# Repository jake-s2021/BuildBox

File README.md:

# BuildBox
Respository containing the files to make a BuildBox leverless arcade stick

The G-Code Files are for an Elegoo Neptune 3 Pro, if you have another printer, do not use them; Slice your own.

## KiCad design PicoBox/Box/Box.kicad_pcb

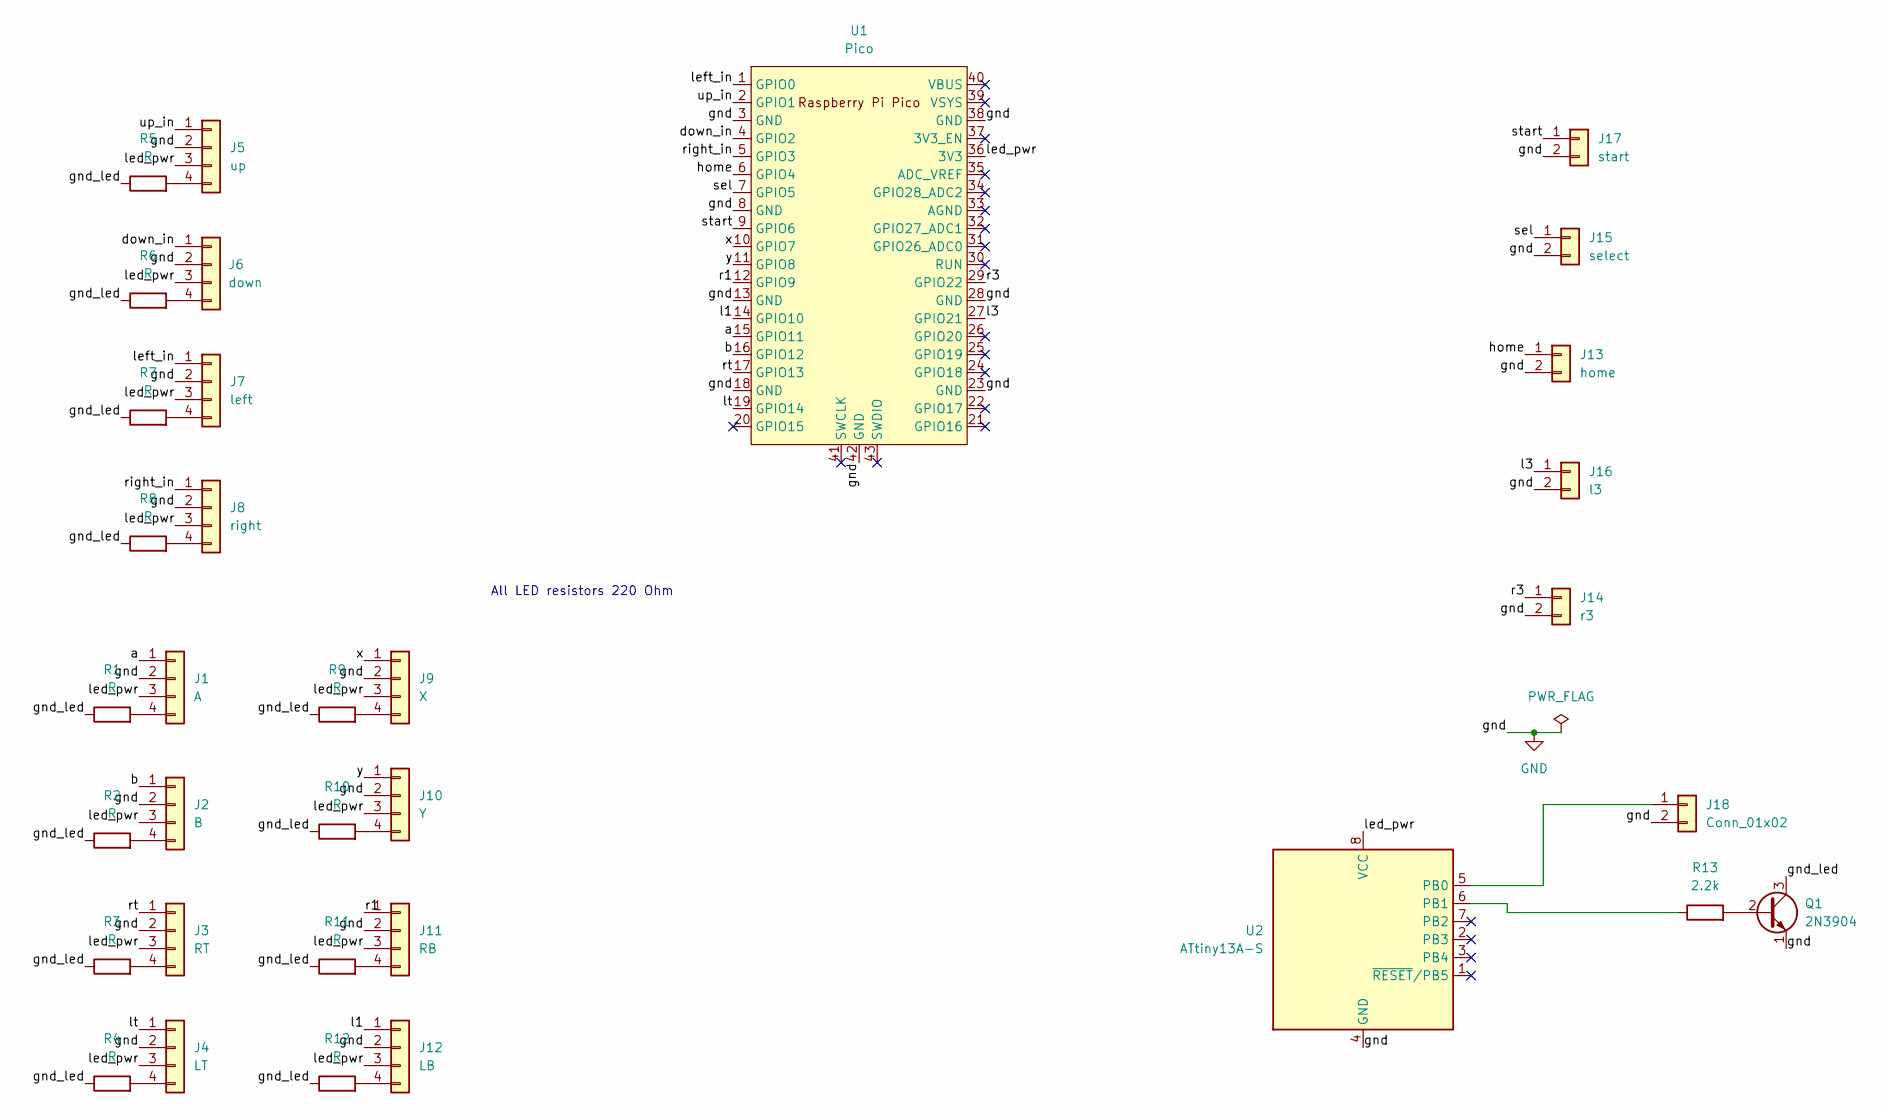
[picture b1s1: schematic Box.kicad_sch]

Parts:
J1: A; MX-Hotswap-1U-LED
J2: B; MX-Hotswap-1U-LED
J3: RT; MX-Hotswap-1U-LED
J4: LT; MX-Hotswap-1U-LED
J5: up; MX-Hotswap-1U-LED
J6: down; MX-Hotswap-1U-LED
J7: left; MX-Hotswap-1U-LED
J8: right; MX-Hotswap-1U-LED
J9: X; MX-Hotswap-1U-LED
J10: Y; MX-Hotswap-1U-LED
J11: RB; MX-Hotswap-1U-LED
J12: LB; MX-Hotswap-1U-LED
J13: home; Silicone_Button_2pin_7.4x7.4
J14: r3; Silicone_Button_2pin_7.4x7.4
J15: select; Silicone_Button_2pin_7.4x7.4
J16: l3; Silicone_Button_2pin_7.4x7.4
J17: start; Silicone_Button_2pin_7.4x7.4
J18: Conn_01x02; Silicone_Button_2pin_7.4x7.4
Q1: 2N3904; TO-92_Inline
R1, R2, R3, R4, R5, R6, R7, R8, R9, R10, R11, R12: R; R_Axial_DIN0204_L3.6mm_D1.6mm_P7.62mm_Horizontal
R13: 2.2k; R_Axial_DIN0204_L3.6mm_D1.6mm_P7.62mm_Horizontal
U1: Pico; RPi_Pico_SMD_TH
U2: ATtiny13A-S; SOIC-8W_5.3x5.3mm_P1.27mm

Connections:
/a: J1.1, U1.15 (GPIO11)
/b: J2.1, U1.16 (GPIO12)
/down_in: J6.1, U1.4 (GPIO2)
/gnd_led: Q1.3 (C), R1.1, R2.1, R3.1, R4.1, R5.1, R6.1, R7.1, R8.1, R9.1, R10.1, R11.1, R12.1
/home: J13.1, U1.6 (GPIO4)
/l1: J12.1, U1.14 (GPIO10)
/l3: J16.1, U1.27 (GPIO21)
/led_pwr: J1.3, J2.3, J3.3, J4.3, J5.3, J6.3, J7.3, J8.3, J9.3, J10.3, J11.3, J12.3, U1.36 (3V3), U2.8 (VCC)
/left_in: J7.1, U1.1 (GPIO0)
/lt: J4.1, U1.19 (GPIO14)
/r1: J11.1, U1.12 (GPIO9)
/r3: J14.1, U1.29 (GPIO22)
/right_in: J8.1, U1.5 (GPIO3)
/rt: J3.1, U1.17 (GPIO13)
/sel: J15.1, U1.7 (GPIO5)
/start: J17.1, U1.9 (GPIO6)
/up_in: J5.1, U1.2 (GPIO1)
/x: J9.1, U1.10 (GPIO7)
/y: J10.1, U1.11 (GPIO8)
GND: J1.2, J2.2, J3.2, J4.2, J5.2, J6.2, J7.2, J8.2, J9.2, J10.2, J11.2, J12.2, J13.2, J14.2, J15.2, J16.2, J17.2, J18.2, Q1.1 (E), U1.3 (GND), U1.8 (GND), U1.13 (GND), U1.18 (GND), U1.23 (GND), U1.28 (GND), U1.38 (GND), U1.42 (GND), U2.4 (GND)
unnamed: J1.4, R1.2
unnamed: J2.4, R2.2
unnamed: J3.4, R3.2
unnamed: J4.4, R4.2
unnamed: J5.4, R5.2
unnamed: J6.4, R6.2
unnamed: J7.4, R7.2
unnamed: J8.4, R8.2
unnamed: J9.4, R9.2
unnamed: J10.4, R10.2
unnamed: J11.4, R11.2
unnamed: J12.4, R12.2
unnamed: J18.1, U2.5 (PB0)
unnamed: Q1.2 (B), R13.2
unnamed: R13.1, U2.6 (PB1)

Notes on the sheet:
All LED resistors 220 Ohm

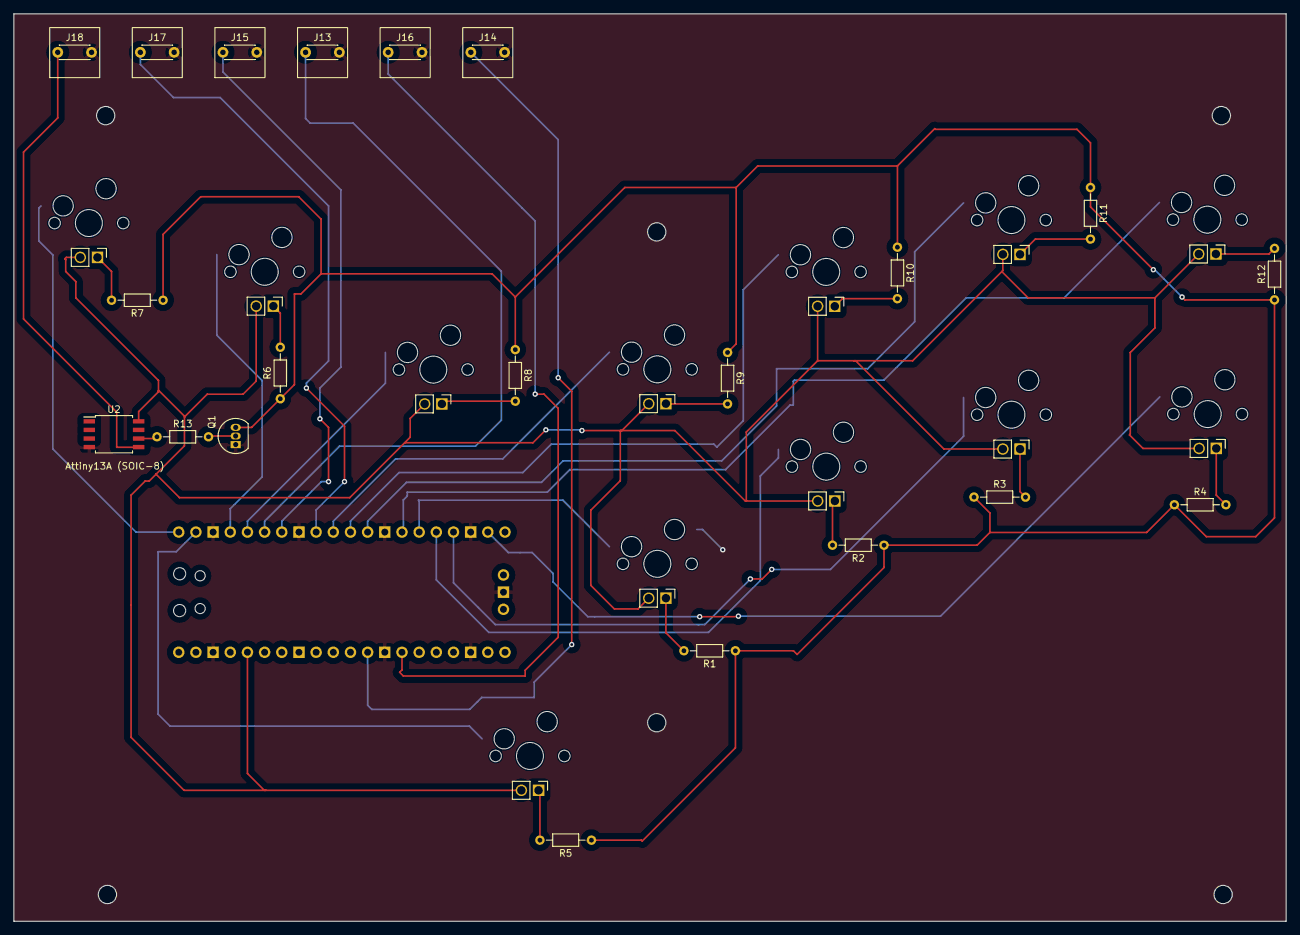
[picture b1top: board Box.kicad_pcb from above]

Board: 2 copper layers, 188.2 x 134.2 mm, 34 parts (1 on the bottom side), 35 nets.
